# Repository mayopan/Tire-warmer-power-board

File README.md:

# Tire-warmer-power-board

  This is the software for seeeduino xiao on the original replacement power board of G-FORCE TYRE WARMER.
  http://www.gforce-hobby.jp/products/G0033.html
  
  Xiao senses temparature of 4 tires with ADS1115.
  Xiao controls 4 heater output for each tire with PWM PID.
  User interface is the same as the G-FORCE one, but the interface board is new.
  mcp23017 on it controls 1602 LCD and 4 button inputs through I2C connection with xiao.
  It's like Adafruit LCD keypad board.
  https://learn.adafruit.com/adafruit-16x2-character-lcd-plus-keypad-for-raspberry-pi
  
  If you want to know schematic, PCB layout, LTSpice sim, refer to github site below.
  https://github.com/mayopan/Tire-warmer-power-board.git

  Date:       January 29, 2022
  Copyright:  mayopan = ROUTE 246 GARAGE
  License:    MIT. See license file for more information but you can basically do whatever you want with this code.

  Dependancy: It uses 2 library for ADC and LCD. LCD library is wrapped in the TireWarmer library.
    * https://github.com/wollewald/ADS1115_WE.git
    * lincomatic/LiquidTWI2 @ ^1.2.7

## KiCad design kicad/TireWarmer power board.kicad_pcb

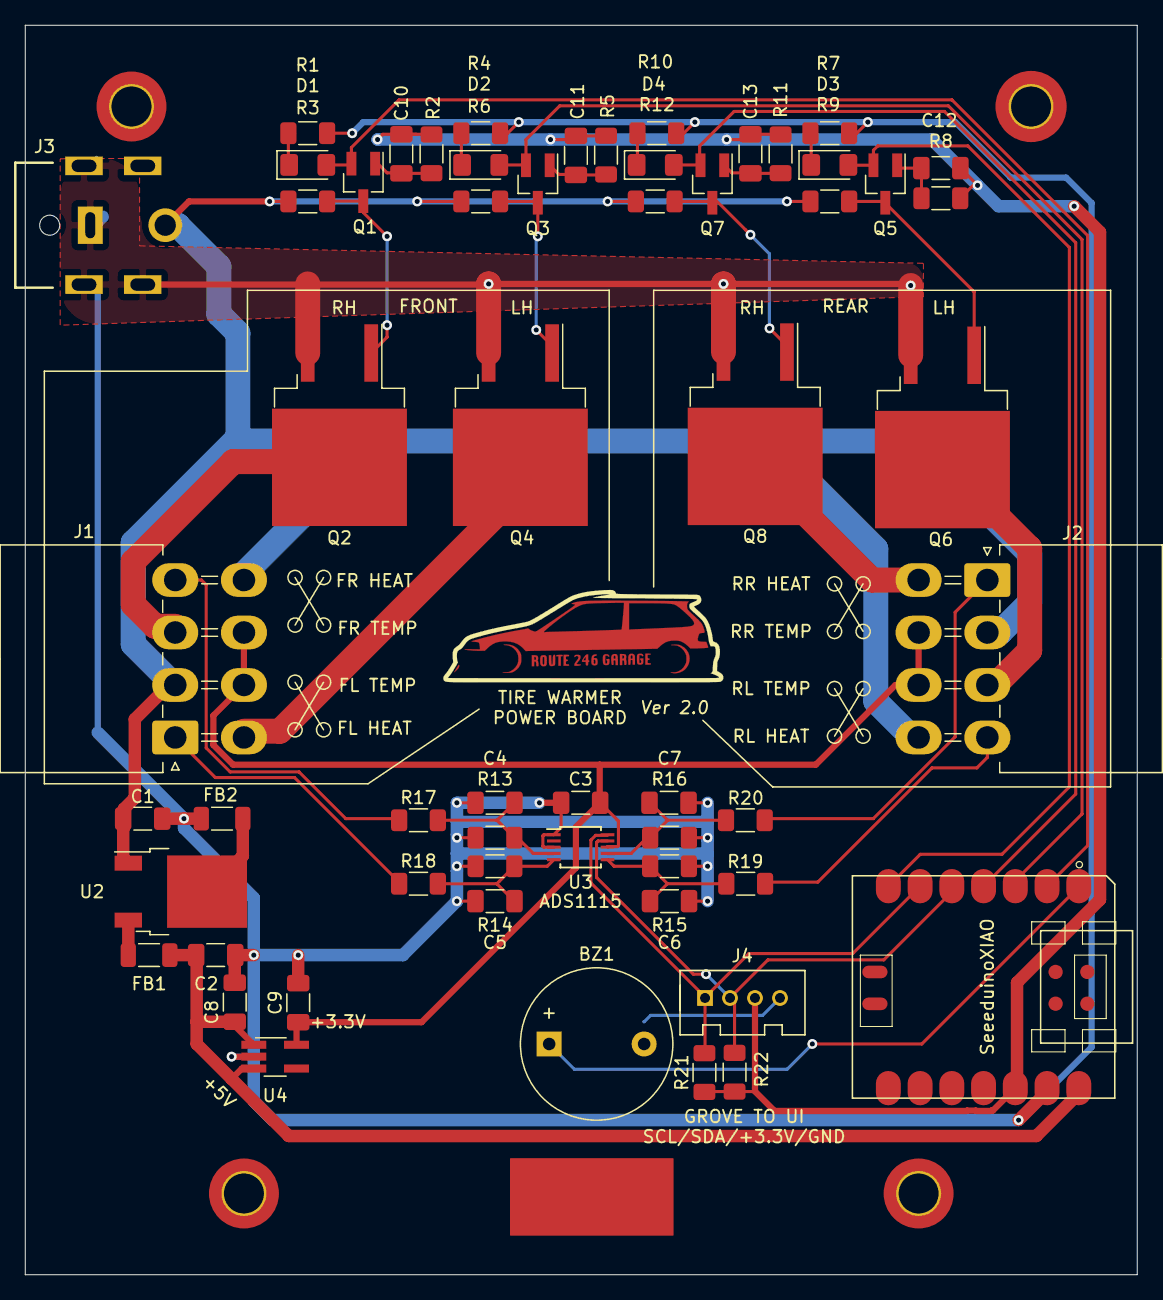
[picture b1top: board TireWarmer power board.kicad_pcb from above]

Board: 2 copper layers, 89.0 x 100.0 mm, 58 parts (0 on the bottom side), 38 nets.

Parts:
BZ1: Buzzer; Buzzer_12x9.5RM7.6
C1, C4, C5, C6, C7: 100n; C_1206_3216Metric_Pad1.33x1.80mm_HandSolder
C2, C3, C8, C9, C10, C11, C12, C13: 1u; C_1206_3216Metric_Pad1.33x1.80mm_HandSolder
D1, D2, D3, D4: LED; LED_1206_3216Metric_Pad1.42x1.75mm_HandSolder
FB1, FB2: 1.5k; L_1206_3216Metric_Pad1.22x1.90mm_HandSolder
J1, J2: Morex mini-fit jr 5569-08A2; Molex_Mini-Fit_Jr_5569-08A2_2x04_P4.20mm_Horizontal
J3: Jack-DC; CUI_PJ-082BH
J4: GROVE-CONNECTOR-DIP_4P-2.0_; HW4-2.0
Q1, Q3, Q5, Q7: BSS138; SOT-23_Handsoldering
Q2, Q4, Q6, Q8: IRF3205; TO-263-2
R1, R4, R7, R10: 150; R_1206_3216Metric_Pad1.30x1.75mm_HandSolder
R2, R5, R8, R11: 10k; R_1206_3216Metric_Pad1.30x1.75mm_HandSolder
R3, R6, R9, R12, R21, R22: 1k; R_1206_3216Metric_Pad1.30x1.75mm_HandSolder
R13, R14, R15, R16: 12k; R_1206_3216Metric_Pad1.30x1.75mm_HandSolder
R17, R18, R19, R20: 7.5k; R_1206_3216Metric_Pad1.30x1.75mm_HandSolder
U1: SeeeduinoXIAO; Seeeduino XIAO-MOUDLE14P-2.54-21X17.8MM
U2: LM78M05; TO-252-2
U3: ADS1115IDGS; TSSOP-10_3x3mm_P0.5mm
U4: ADP151TUJZ3.3-EPR2; TSOT-23-5_HandSoldering

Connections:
+3.3VA: C3.1, C9.1, J1.6, J1.7, J2.6, J2.7, U3.8, U4.5
+3V3: C10.1, C11.1, C12.1, C13.1, J4.3, R2.1, R5.1, R8.1, R11.1, R21.1, R22.1, U1.12
+5V: C2.1, C8.1, FB1.1, U1.14, U4.1, U4.3
+12V: C1.1, J1.2, J1.8, J2.2, J2.8, J3.1, R3.1, R6.2, R9.1, R12.1, U2.1
GND: BZ1.2, C1.2, C2.2, C3.2, C4.2, C5.2, C6.2, C7.2, C8.2, C9.2, FB2.2, J3.2, J4.4, Q2.3, Q4.3, Q6.3, Q8.3, R1.2, R4.2, R7.2, R10.2, R13.2, R14.2, R15.2, R16.2, U1.13, U3.1, U3.3, U4.2
unnamed: BZ1.1, U1.1
unnamed: C4.1, R13.1, R17.2, U3.4
unnamed: C5.1, R14.1, R18.2, U3.5
unnamed: C6.1, R15.1, R19.2, U3.6
unnamed: C7.1, R16.1, R20.2, U3.7
unnamed: C10.2, Q1.1, R2.2
unnamed: C11.2, Q3.1, R5.2
unnamed: C12.2, Q5.1, R8.2
unnamed: C13.2, Q7.1, R11.2
unnamed: D1.1, R1.1
unnamed: D1.2, Q1.2, U1.2
unnamed: D2.1, R4.1
unnamed: D2.2, Q3.2, U1.3
unnamed: D3.1, R7.1
unnamed: D3.2, Q5.2, U1.7
unnamed: D4.1, R10.1
unnamed: D4.2, Q7.2, U1.4
unnamed: FB1.2, U2.3
unnamed: FB2.1, U2.2
unnamed: J1.1, R18.1
unnamed: J1.3, Q2.2
unnamed: J1.4, R17.1
unnamed: J1.5, Q4.2
unnamed: J2.1, R20.1
unnamed: J2.3, Q6.2
unnamed: J2.4, R19.1
unnamed: J2.5, Q8.2
unnamed: J4.1, R21.2, U1.6, U3.10
unnamed: J4.2, R22.2, U1.5, U3.9
unnamed: Q1.3, Q2.1, R3.2
unnamed: Q3.3, Q4.1, R6.1
unnamed: Q5.3, Q6.1, R9.2
unnamed: Q7.3, Q8.1, R12.2

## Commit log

2022-01-28 comment add
